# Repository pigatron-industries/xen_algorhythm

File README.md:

# AlgoRhythm

Eurorack algorithmic rhythm generator.

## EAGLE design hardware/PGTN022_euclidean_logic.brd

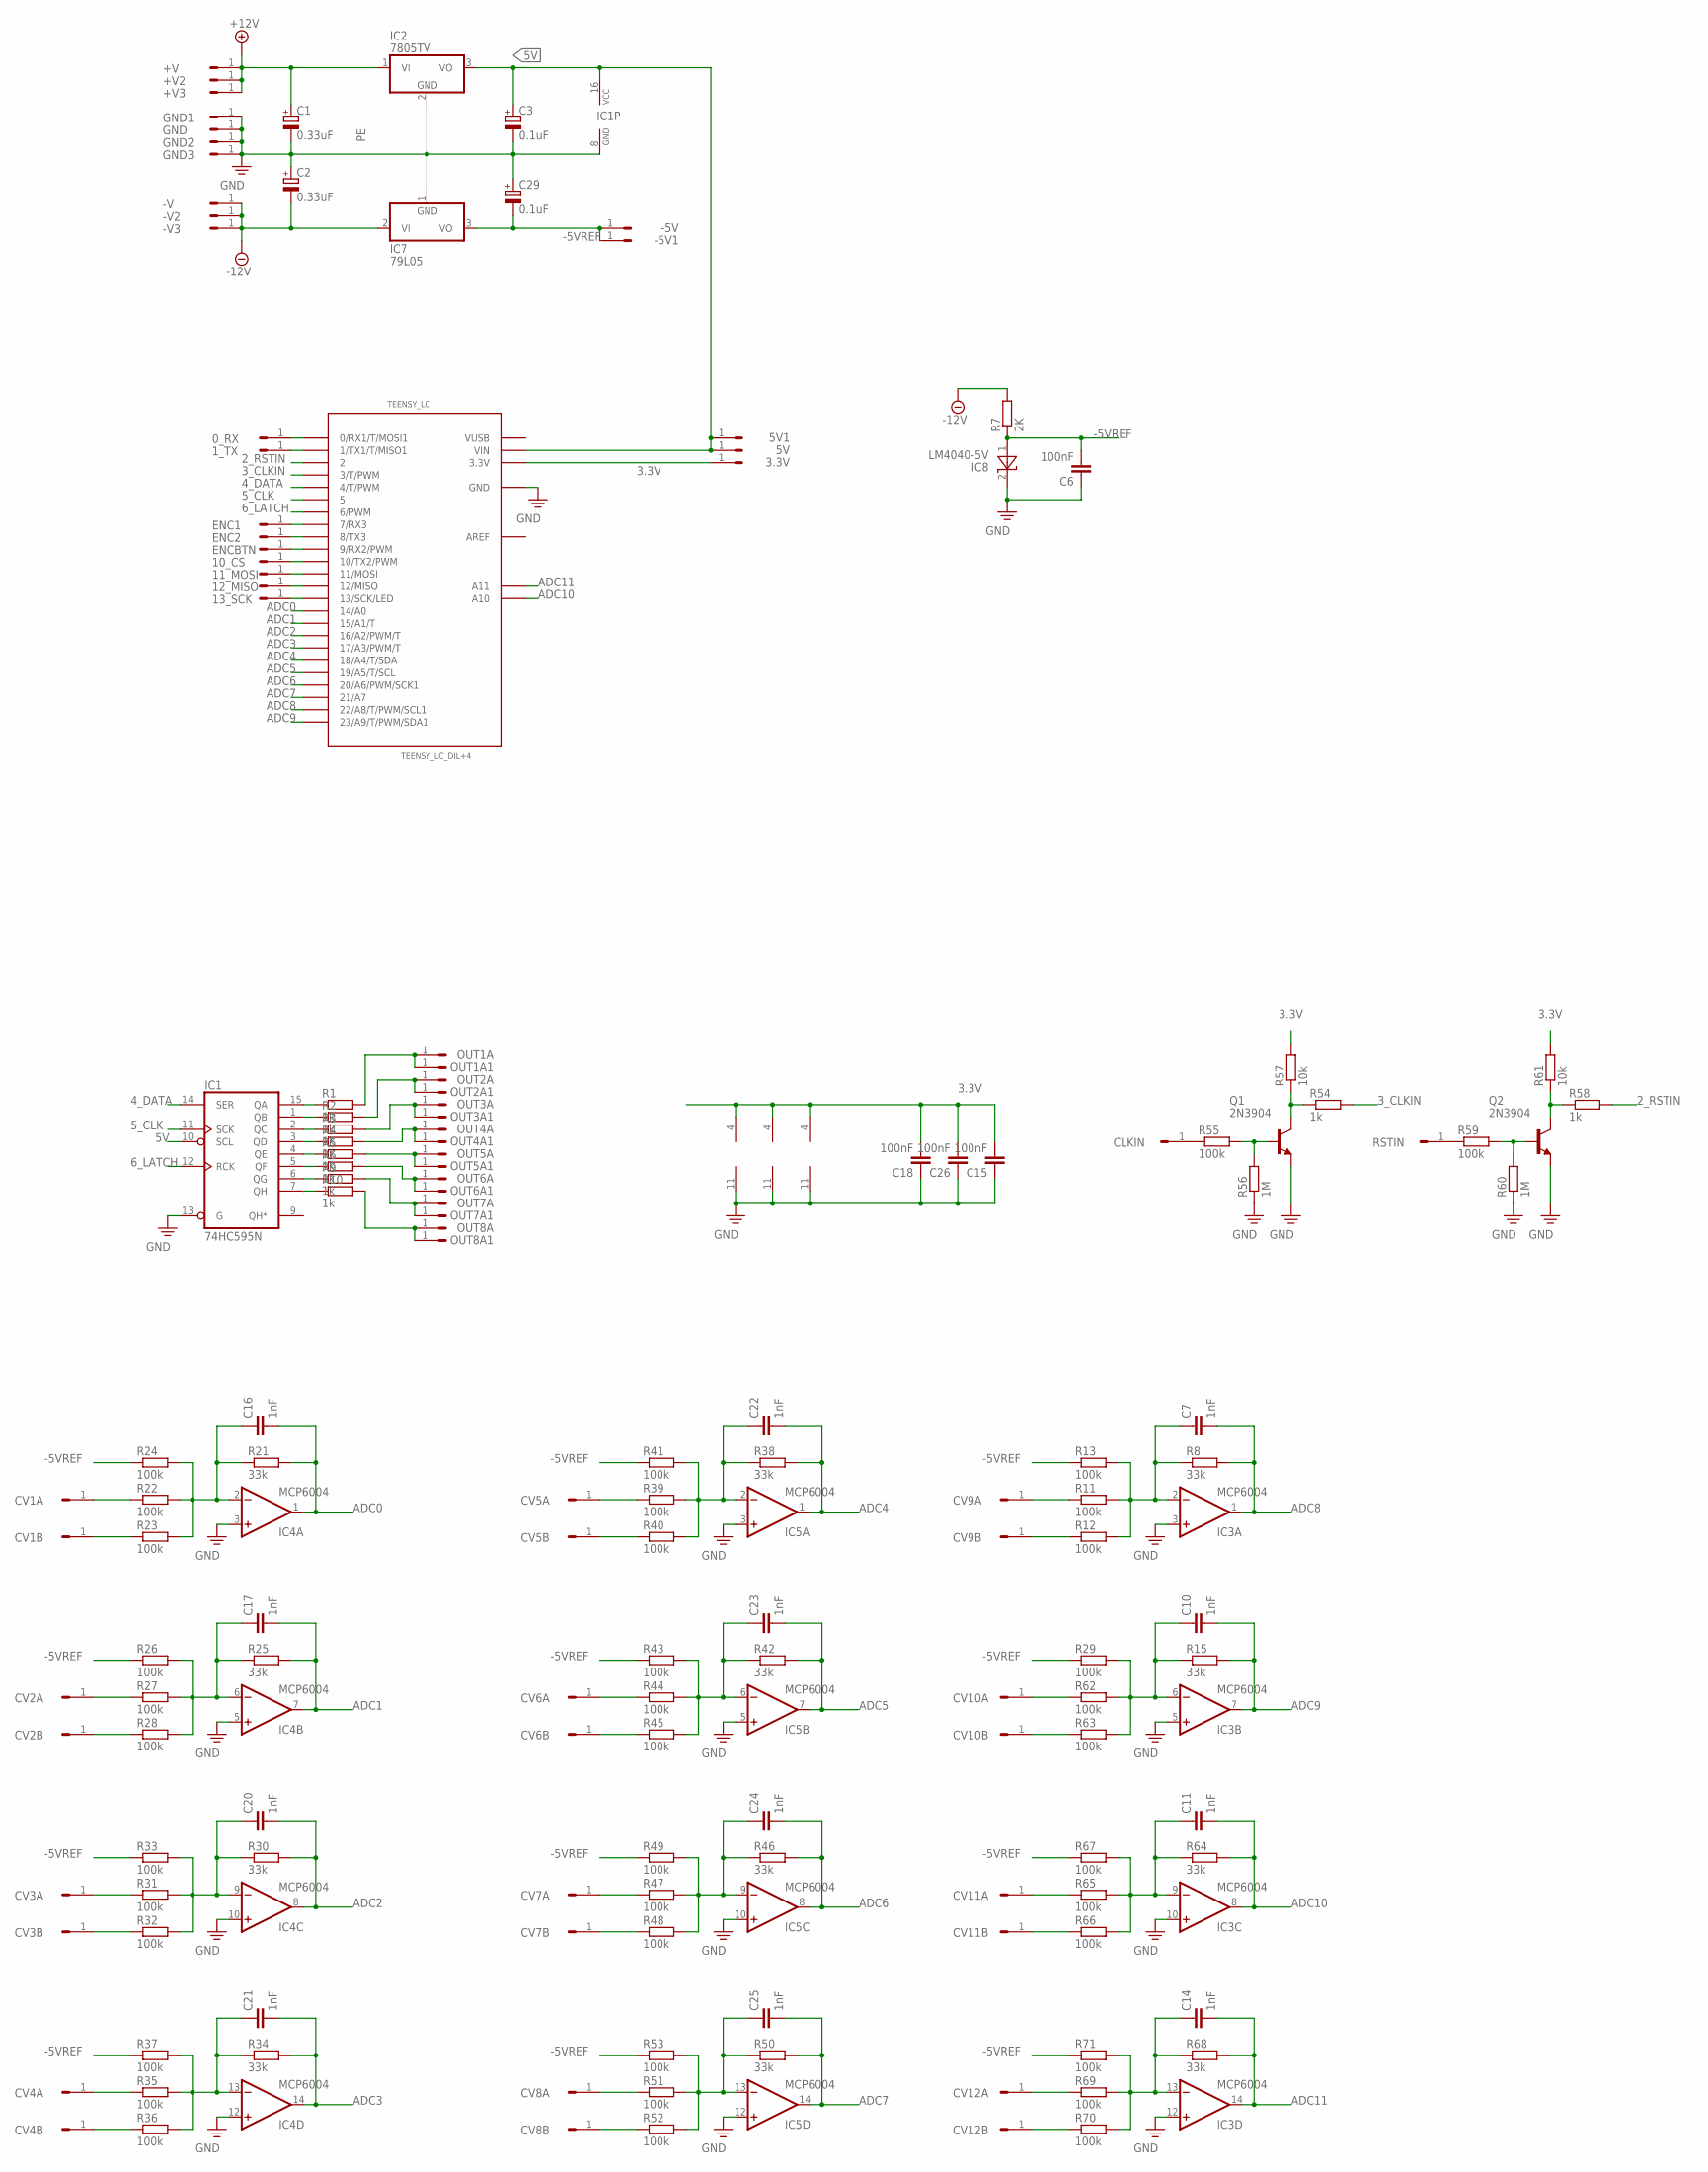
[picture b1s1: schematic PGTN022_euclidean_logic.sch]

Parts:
0_RX, 1_TX, 3.3V, 5V, 5V1, 10_CS, 11_MOSI, 12_MISO, 13_SCK: HEADER/MALE/01
+V, +V2, +V3: HEADER/MALE/01
-5V, -5V1: HEADER/MALE/01
-V, -V2, -V3: HEADER/MALE/01
C1, C2: 0.33uF; E2,5-6
C3, C29: 0.1uF; E2,5-6
C6, C15, C18, C26: 100nF; CERAMICDISC/5
C7, C10, C11, C14, C16, C17, C20, C21, C22, C23, C24, C25: 1nF; CERAMICDISC/5
CLKIN: HEADER/MALE/01
CV1A, CV1B, CV2A, CV2B, CV3A, CV3B, CV4A, CV4B, CV5A, CV5B, CV6A, CV6B, CV7A, CV7B, CV8A, CV8B, CV9A, CV9B, CV10A, CV10B, CV11A, CV11B, CV12A, CV12B: HEADER/MALE/01
ENC1, ENC2: HEADER/MALE/01
ENCBTN: HEADER/MALE/01
GND, GND1, GND2, GND3: HEADER/MALE/01
IC1: 74HC595N; DIL16
IC2: 7805TV; TO220V
IC3, IC4, IC5: MCP6004; DIL14
IC7: 79L05; TO92
IC8: LM4040-5V; TO92
OUT1A, OUT1A1, OUT2A, OUT2A1, OUT3A, OUT3A1, OUT4A, OUT4A1, OUT5A, OUT5A1, OUT6A, OUT6A1, OUT7A, OUT7A1, OUT8A, OUT8A1: HEADER/MALE/01
Q1, Q2: 2N3904; TO92
R1, R2, R3, R4, R5, R6, R9, R10, R54, R58: 1k; RESISTOR/7.5
R7: 2K; RESISTOR/7.5
R8, R15, R21, R25, R30, R34, R38, R42, R46, R50, R64, R68: 33k; RESISTOR/7.5
R11, R12, R13, R22, R23, R24, R26, R27, R28, R29, R31, R32, R33, R35, R36, R37, R39, R40, R41, R43, R44, R45, R47, R48, R49, R51, R52, R53, R55, R59, R62, R63, R65, R66, R67, R69, R70, R71: 100k; RESISTOR/7.5
R56, R60: 1M; RESISTOR/7.5
R57, R61: 10k; RESISTOR/7.5
RSTIN: HEADER/MALE/01
TEENSY_LC: TEENSY_LC_DIL+4; TEENSY_3.0-3.2&LC_DIL+4

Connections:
2_RSTIN: R58.2, TEENSY_LC.2
3.3V: 3.3V.1, C15.2, C18.2, C26.2, IC3.4 (V+), IC4.4 (V+), IC5.4 (V+), R57.2, R61.2, TEENSY_LC.3.3V
3_CLKIN: R54.2, TEENSY_LC.3 (3/T/PWM)
4_DATA: IC1.14 (SER), TEENSY_LC.4 (4/T/PWM)
5V: 5V.1, 5V1.1, C3.+, IC1.10 (SCL), IC1.16 (VCC), IC2.3 (VO), TEENSY_LC.VIN
5_CLK: IC1.11 (SCK), TEENSY_LC.5
6_LATCH: IC1.12 (RCK), TEENSY_LC.6 (6/PWM)
+12V: +V.1, +V2.1, +V3.1, C1.+, IC2.1 (VI)
-5VREF: -5V.1, -5V1.1, C6.2, C29.-, IC7.3 (VO), IC8.1 (A), R7.1, R13.1, R24.1, R26.1, R29.1, R33.1, R37.1, R41.1, R43.1, R49.1, R53.1, R67.1, R71.1
-12V: -V.1, -V2.1, -V3.1, C2.-, IC7.2 (VI), R7.2
ADC0: C16.2, IC4.1 (OUT), R21.2, TEENSY_LC.14/A0
ADC1: C17.2, IC4.7 (OUT), R25.2, TEENSY_LC.15/A1 (15/A1/T)
ADC2: C20.2, IC4.8 (OUT), R30.2, TEENSY_LC.16/A2 (16/A2/PWM/T)
ADC3: C21.2, IC4.14 (OUT), R34.2, TEENSY_LC.17/A3 (17/A3/PWM/T)
ADC4: C22.2, IC5.1 (OUT), R38.2, TEENSY_LC.18/A4 (18/A4/T/SDA)
ADC5: C23.2, IC5.7 (OUT), R42.2, TEENSY_LC.19/A5 (19/A5/T/SCL)
ADC6: C24.2, IC5.8 (OUT), R46.2, TEENSY_LC.20/A6 (20/A6/PWM/SCK1)
ADC7: C25.2, IC5.14 (OUT), R50.2, TEENSY_LC.21/A7
ADC8: C7.2, IC3.1 (OUT), R8.2, TEENSY_LC.22/A8 (22/A8/T/PWM/SCL1)
ADC9: C10.2, IC3.7 (OUT), R15.2, TEENSY_LC.23/A9 (23/A9/T/PWM/SDA1)
ADC10: C11.2, IC3.8 (OUT), R64.2, TEENSY_LC.A10
ADC11: C14.2, IC3.14 (OUT), R68.2, TEENSY_LC.A11
AREF: TEENSY_LC.AREF
unnamed: CV2A.1, R27.1
unnamed: IC1.15 (QA), R1.1
unnamed: OUT1A.1, OUT1A1.1, R1.2
unnamed: IC1.1 (QB), R2.1
unnamed: IC1.2 (QC), R3.1
unnamed: IC1.3 (QD), R4.1
unnamed: IC1.4 (QE), R5.1
unnamed: C7.1, IC3.2 (-IN), R8.1, R11.2, R12.2, R13.2
unnamed: IC1.5 (QF), R6.1
unnamed: IC1.6 (QG), R9.1
unnamed: IC1.7 (QH), R10.1
unnamed: OUT8A.1, OUT8A1.1, R10.2
unnamed: CV9B.1, R12.1
unnamed: CV9A.1, R11.1
unnamed: OUT2A.1, OUT2A1.1, R2.2
unnamed: C10.1, IC3.6 (-IN), R15.1, R29.2, R62.2, R63.2
unnamed: OUT3A.1, OUT3A1.1, R3.2
unnamed: CV10A.1, R62.1
unnamed: CV10B.1, R63.1
unnamed: OUT4A.1, OUT4A1.1, R4.2
unnamed: OUT5A.1, OUT5A1.1, R5.2
unnamed: CV1A.1, R22.1
unnamed: C16.1, IC4.2 (-IN), R21.1, R22.2, R23.2, R24.2
unnamed: R59.1, RSTIN.1
unnamed: CV2B.1, R28.1
unnamed: CV1B.1, R23.1
unnamed: OUT6A.1, OUT6A1.1, R6.2
unnamed: C17.1, IC4.6 (-IN), R25.1, R26.2, R27.2, R28.2
unnamed: C21.1, IC4.13 (-IN), R34.1, R35.2, R36.2, R37.2
unnamed: CV4A.1, R35.1
unnamed: CV4B.1, R36.1
unnamed: OUT7A.1, OUT7A1.1, R9.2
unnamed: CV3B.1, R32.1
unnamed: CV3A.1, R31.1
unnamed: C20.1, IC4.9 (-IN), R30.1, R31.2, R32.2, R33.2
unnamed: 12_MISO.1, TEENSY_LC.12 (12/MISO)
unnamed: C22.1, IC5.2 (-IN), R38.1, R39.2, R40.2, R41.2
unnamed: 0_RX.1, TEENSY_LC.0 (0/RX1/T/MOSI1)
unnamed: CV5B.1, R40.1
unnamed: CV5A.1, R39.1
unnamed: 1_TX.1, TEENSY_LC.1 (1/TX1/T/MISO1)
unnamed: C23.1, IC5.6 (-IN), R42.1, R43.2, R44.2, R45.2
unnamed: CV6A.1, R44.1
unnamed: CV6B.1, R45.1
unnamed: C25.1, IC5.13 (-IN), R50.1, R51.2, R52.2, R53.2
unnamed: ENC1.1, TEENSY_LC.7 (7/RX3)
unnamed: CV8A.1, R51.1
unnamed: CV8B.1, R52.1
unnamed: CV7B.1, R48.1
unnamed: CV7A.1, R47.1
unnamed: C24.1, IC5.9 (-IN), R46.1, R47.2, R48.2, R49.2
unnamed: ENC2.1, TEENSY_LC.8 (8/TX3)
unnamed: CLKIN.1, R55.1
unnamed: Q1.2 (B), R55.2, R56.2
unnamed: Q1.1 (C), R54.1, R57.1
unnamed: C14.1, IC3.13 (-IN), R68.1, R69.2, R70.2, R71.2
unnamed: Q2.2 (B), R59.2, R60.2
unnamed: Q2.1 (C), R58.1, R61.1
unnamed: CV12A.1, R69.1
unnamed: ENCBTN.1, TEENSY_LC.9 (9/RX2/PWM)
unnamed: 10_CS.1, TEENSY_LC.10 (10/TX2/PWM)
unnamed: 11_MOSI.1, TEENSY_LC.11 (11/MOSI)
unnamed: 13_SCK.1, TEENSY_LC.13 (13/SCK/LED)
unnamed: CV12B.1, R70.1
unnamed: CV11B.1, R66.1
unnamed: CV11A.1, R65.1
unnamed: C11.1, IC3.9 (-IN), R64.1, R65.2, R66.2, R67.2
PE: C1.-, C2.+, C3.-, C6.1, C15.1, C18.1, C26.1, C29.+, GND.1, GND1.1, GND2.1, GND3.1, IC1.8 (GND), IC1.13 (G), IC2.2 (GND), IC3.3 (+IN), IC3.5 (+IN), IC3.10 (+IN), IC3.11 (V-), IC3.12 (+IN), IC4.3 (+IN), IC4.5 (+IN), IC4.10 (+IN), IC4.11 (V-), IC4.12 (+IN), IC5.3 (+IN), IC5.5 (+IN), IC5.10 (+IN), IC5.11 (V-), IC5.12 (+IN), IC7.1 (GND), IC8.2 (C), Q1.3 (E), Q2.3 (E), R56.1, R60.1, TEENSY_LC.AGND (GND), TEENSY_LC.GND
VUSB: TEENSY_LC.VUSB

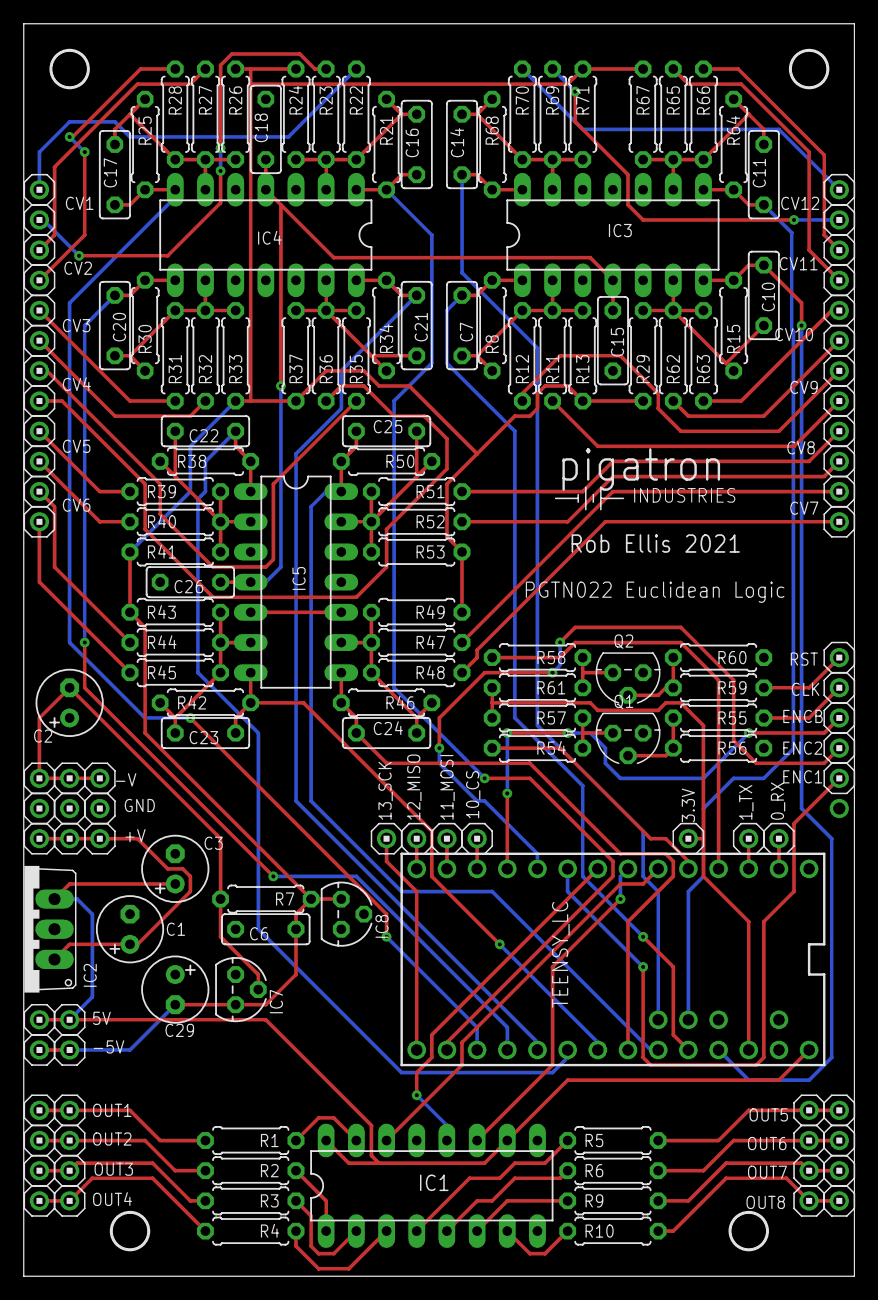
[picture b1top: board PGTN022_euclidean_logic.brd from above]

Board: 2 copper layers, 69.9 x 105.4 mm, 166 parts (1 on the bottom side), 90 nets.

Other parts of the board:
U$1: PIGATRON-LOGO
U$2, U$3, U$4, U$5: STANDOFF/3.0

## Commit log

2021-04-06 Commit all code
2021-04-06 make density and offset controls got from 0 to 100% of length
2021-04-06 Make density go to full
2021-04-07 Make encoder push button do a reset
2021-04-07 Refactor some stuff and add modes
2021-04-08 synced channels mode
2021-04-08 Refactor main controller logic into sperate euclidean controller
2021-04-08 renamed to EuclideanChannel
2021-04-08 added logic gates
2021-04-08 update density and offset when length changes
2021-04-10 use interrupt based trigger input to detect shorter pulses
2021-04-17 Dual sequential mode
2021-05-26 Clock Divider mode
2021-05-30 Added clock divider mode
2021-07-22 Use template class for push button
2021-12-27 Update eurorack library
2021-12-28 Select controllers in build config. Save mode to eeprom
2021-12-28 Remove unneeded code
2021-12-28 Moved main controller functions into abstract class
2021-12-28 Moved AbstractMainController and Config to eurorack library
2021-12-29 use HC595Device class
2022-01-01 support mark 2 hardware
2022-01-02 Moved common clock methods to Controller subclass
2022-01-04 Use extra outputs in decoder
2022-02-02 Update MainController to use new template
2022-02-04 Use RotaryEncoderButton
2022-02-09 Fix mki compile errors
2022-03-16 use init and send function on device
2022-03-17 receive input values
2022-03-18 Use new version of TriggerInput
2022-03-18 Fixed some issues with synchronous mode
